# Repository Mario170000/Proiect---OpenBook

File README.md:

# Proiect---OpenBook
Proiectarea unui e-book reader open book

BOM:

| Qty | Value                   | Device                                                          | Parts                                                    | Description                                                                                                                                                                                                                           | WHERE_TO_BUY                                                                                                                                                                              | DATASHEET                                                                                                                            |
|-----|-------------------------|-----------------------------------------------------------------|----------------------------------------------------------|---------------------------------------------------------------------------------------------------------------------------------------------------------------------------------------------------------------------------------------|--------------------------------------------------------------------------------------------------------------------------------------------------------------------------------------------|-------------------------------------------------------------------------------------------------------------------------------------|
| 1   |                         | ADAFRUIT_LEDCHIP-LED0603                                        | CHG_LED                                                   | LED                                                                                                                                                                                                                                   | [link](https://ro.mouser.com/ProductDetail/BJB/35.116.1007-001-01?qs=iLKYxzqNS76jqQb6thkyzg%3D%3D)                                                                                          | [link](https://ro.mouser.com/datasheet/2/904/BJBDE_6680739_v3_Datasheet_35_116_1007_85_Optics4x-3193726.pdf)                                           |
| 3   |                         | EAGLE-LTSPICE_CC0402                                            | C4_USB, C5_USB, C17                                       | CAPACITOR, European symbol                                                                                                                                                                                                            | [link](https://ro.mouser.com/ProductDetail/YAGEO/CC0402KRX7R5BB474?qs=tS%2FAHvPQ%2F56tORtAcxAOhQ%3D%3D)                                                                                       | [link](https://ro.mouser.com/datasheet/2/447/UPY_GPHC_X7R_6_3V_to_250V_24-3441574.pdf)                                              |
| 1   |                         | SJ                                                              | SJ1                                                      | SMD solder JUMPER                                                                                                                                                                                                                     | [link](https://ro.mouser.com/ProductDetail/Amphenol-FCI/71363-302LF?qs=QPQicS5vByJvpVjU0oRgsQ%3D%3D)                                                                                        | [link](https://cdn.amphenol-cs.com/media/wysiwyg/files/documentation/datasheet/boardwiretoboard/bwb_dubox_shunts.pdf)                                 |
| 1   | 0.1uF/50V               | EAGLE-LTSPICE_CC0402                                            | EPD_C5                                                    | CAPACITOR, European symbol                                                                                                                                                                                                            | [link](https://ro.mouser.com/ProductDetail/YAGEO/CC0402JRX7R8BB104?qs=tS%2FAHvPQ%2F56C6Jcuby2Lxg%3D%3D)                                                                                        | [link](https://ro.mouser.com/datasheet/2/447/UPY_GPHC_X7R_6_3V_to_250V_24-3441574.pdf)                                              |
| 1   | 0.47                    | ESP32_WROVER_EAGLE-LTSPICE_RR0402                               | R4                                                        | RESISTOR, European symbol                                                                                                                                                                                                             | [link](https://ro.mouser.com/ProductDetail/Vishay/PFRR0402Y2101WBT?qs=iLKYxzqNS75ICTUqzuuuLQ%3D%3D)                                                                                           | [link](https://www.vishay.com/doc?53046)                                                                                                             |
| 1   | 100K                    | ESP32_WROVER_EAGLE-LTSPICE_RR0402                               | R1_PWRUSB                                                 | RESISTOR, European symbol                                                                                                                                                                                                             | [link](https://ro.mouser.com/ProductDetail/Vishay/PFRR0402Y1003WBT?qs=iLKYxzqNS76UwFIGpGXUcw%3D%3D)                                                                                           | [link](https://www.vishay.com/doc?53046)                                                                                                             |
| 7   | 100nF                   | EAGLE-LTSPICE_CC0402                                            | C1, C2, C6, C8, C9, C10, C_DELAY                          | CAPACITOR, European symbol                                                                                                                                                                                                            | [link](https://ro.mouser.com/ProductDetail/YAGEO/CC0402KRX7R5BB474?qs=tS%2FAHvPQ%2F56tORtAcxAOhQ%3D%3D)                                                                                       | [link](https://ro.mouser.com/datasheet/2/447/UPY_GPHC_X7R_6_3V_to_250V_24-3441574.pdf)                                              |
| 1   | 100uF                   | RCL_CPOL-EUCT3528                                               | C3                                                        | POLARIZED CAPACITOR, European symbol                                                                                                                                                                                                  | [link](https://ro.mouser.com/ProductDetail/Panasonic/EEU-FS1K101L?qs=sGAEpiMZZMvwFf0viD3Y3fHxNcSaiftwbgqrEa58hlq7Mz20qWHEdw%3D%3D)                                                              | [link](https://www.mouser.com/catalog/specsheets/Panasonic_08082018_Capacitor%20Radial%20Leaded%20Lytic%20(EEU-FS)%20020118.pdf)                      |
| 12  | 10K                     | ESP32_WROVER_EAGLE-LTSPICE_RR0402                               | R1_PINH, R1_PINH1, R2-PINH1, R2_PINH, R3, R5, R6, R7, R8, R9, R10, R_CL1 | RESISTOR, European symbol                                                                                                                                                                                                             | [link](https://ro.mouser.com/ProductDetail/Vishay/PFRR0402Y1002WBT?qs=iLKYxzqNS75QPApzdnOraw%3D%3D)                                                                                           | [link](https://www.vishay.com/doc?53046)                                                                                                             |
| 3   | 10k                     | ESP32_WROVER_EAGLE-LTSPICE_RR0402                               | R_BOOT, R_CHANGE, R_RESET                                 | RESISTOR, European symbol                                                                                                                                                                                                             | [link](https://ro.mouser.com/ProductDetail/Vishay/PFRR0402Y1002WBT?qs=iLKYxzqNS75QPApzdnOraw%3D%3D)                                                                                           | [link](https://www.vishay.com/doc?53046)                                                                                                             |
| 1   | 10uF                    | EAGLE-LTSPICE_CC0402                                            | C7                                                        | CAPACITOR, European symbol                                                                                                                                                                                                            | [link](https://ro.mouser.com/ProductDetail/YAGEO/CC0402MRX5R4BB106?qs=tS%2FAHvPQ%2F561gTjBOiVihQ%3D%3D)                                                                                        | [link](https://ro.mouser.com/datasheet/2/447/upy_gphc_x5r_4v_to_50v-3461255.pdf)                                                  |
| 1   | 112A-TAAR-R03_ATTEND                                        | 112A-TAAR-R03_ATTEND                                        | J4                                                        | Micro SD Card Socket, Push-Push Type, Top Mount, SMT, H=1.83mm, 10u                                                                                                                                                                    | [link](https://ro.mouser.com/ProductDetail/Swissbit/SFSD256GL2AM1TO-E-8H-231-STD?qs=%252BXxaIXUDbq3EiR9fdqsT0g%3D%3D)                                                                           | [link](https://ro.mouser.com/datasheet/2/615/Swissbit_02_03_2025_S_50_data_sheet-3561244.pdf)                                                         |
| 1   | 15                      | ESP32_WROVER_EAGLE-LTSPICE_RR0402                               | R_CAPACITOR                                               | RESISTOR, European symbol                                                                                                                                                                                                             | [link](https://ro.mouser.com/ProductDetail/Vishay/PFRR0402Y1002WBT?qs=iLKYxzqNS75QPApzdnOraw%3D%3D)                                                                                           | [link](https://www.vishay.com/doc?53046)                                                                                                             |
| 1   | 1uF                     | EAGLE-LTSPICE_CC0402                                            | C5                                                        | CAPACITOR, European symbol                                                                                                                                                                                                            | [link](https://ro.mouser.com/ProductDetail/YAGEO/CC0402KPX7R9BB332?qs=tS%2FAHvPQ%2F56Ev%2FR70%252BDkow%3D%3D)                                                                                   | [link](https://ro.mouser.com/datasheet/2/447/UPY_GPHC_X7R_6_3V_to_250V_24-3441574.pdf)                                              |
| 9   | 1uF/50V                 | EAGLE-LTSPICE_CC0402                                            | EPD_C1, EPD_C2, EPD_C6, EPD_C7, EPD_C8, EPD_C9, EPD_C10, EPD_C11, EPD_C12 | CAPACITOR, European symbol                                                                                                                                                                                                            | [link](https://ro.mouser.com/ProductDetail/YAGEO/CC0402KPX7R9BB332?qs=tS%2FAHvPQ%2F56Ev%2FR70%252BDkow%3D%3D)                                                                                   | [link](https://ro.mouser.com/datasheet/2/447/UPY_GPHC_X7R_6_3V_to_250V_24-3441574.pdf)                                              |
| 1   | 2.2                     | ESP32_WROVER_EAGLE-LTSPICE_RR0402                               | R2                                                        | RESISTOR, European symbol                                                                                                                                                                                                             | [link](https://ro.mouser.com/ProductDetail/Vishay/PFRR0402Y2201WBT?qs=iLKYxzqNS76BFrJRYiyDBw%3D%3D)                                                                                           | [link](https://www.vishay.com/doc?53046)                                                                                                             |
| 1   | 200                     | ESP32_WROVER_EAGLE-LTSPICE_RR0402                               | R1_BAT                                                    | RESISTOR, European symbol                                                                                                                                                                                                             | [link](https://ro.mouser.com/ProductDetail/Vishay/PFRR0402Y2101WBT?qs=iLKYxzqNS75ICTUqzuuuLQ%3D%3D)                                                                                           | [link](https://www.vishay.com/doc?53046)                                                                                                             |
| 2   | 20V/4.2A/52mO/1.4W      | ESP32_WROVER_SPARKFUN-DISCRETESEMI_MOSFET_PCH-DMG2305UX-7       | Q1, Q2                                                    | P-channel MOSFETs                                                                                                                                                                                                                     | [link](https://ro.mouser.com/ProductDetail/Diodes-Incorporated/DMG2305UX-7?qs=L1DZKBg7t5F%2FNBHrjfxC%252Bg%3D%3D)                                                                                | [link](https://www.diodes.com/assets/Datasheets/DMG2305UX.pdf)                                                                                         |
| 2   | 2K                      | ESP32_WROVER_EAGLE-LTSPICE_RR0402                               | R1, R2_BAT                                                | RESISTOR, European symbol                                                                                                                                                                                                             | [link](https://ro.mouser.com/ProductDetail/Vishay/PFRR0402Y2001WBT?qs=iLKYxzqNS75yWwLpEkqbdw%3D%3D)                                                                                           | [link](https://www.vishay.com/doc?53046)                                                                                                             |
| 4   | 4.7uF                   | EAGLE-LTSPICE_CC0402                                            | C1_BAT, C1_BAT2, C2_BAT, C4                               | CAPACITOR, European symbol                                                                                                                                                                                                            | [link](https://ro.mouser.com/ProductDetail/YAGEO/CC0402KRX5R6BB105?qs=BKNoF%2F0xMNu0TvpE6ze2Iw%3D%3D)                                                                                         | [link](https://ro.mouser.com/datasheet/2/447/upy_gphc_x5r_4v_to_50v-3461255.pdf)                                                  |
| 1   | 5K1                     | ESP32_WROVER_EAGLE-LTSPICE_RR0402                               | R2-USB1                                                   | RESISTOR, European symbol                                                                                                                                                                                                             | [link](https://ro.mouser.com/ProductDetail/Vishay/PFRR0402E4752BBT?qs=%252BXxaIXUDbq1vDshWgSXpwA%3D%3D)                                                                                         | [link](https://www.vishay.com/doc?53046)                                                                                                             |
| 1   | 5k1                     | ESP32_WROVER_EAGLE-LTSPICE_RR0402                               | R2-USB                                                    | RESISTOR, European symbol                                                                                                                                                                                                             | [link](https://ro.mouser.com/ProductDetail/Vishay/PFRR0402E4752BBT?qs=%252BXxaIXUDbq1vDshWgSXpwA%3D%3D)                                                                                         | [link](https://www.vishay.com/doc?53046)                                                                                                             |
| 1   | 68uH                    | 744043680IND_4828-WE-TPC_WRE                                    | L1                                                        |                                                                                                                                                                                                                                       | [link](https://ro.mouser.com/ProductDetail/Wurth-Elektronik/744043680?qs=PGXP4M47uW6VkZq%252BkzjrHA%3D%3D)                                                                                       | [link](https://www.we-online.com/components/products/datasheet/744043680.pdf)                                                                          |
| 1   | BD5229G-TR              | BD5229G-TR                                                     | IC1                                                       | Voltage Detector with Adjustable Delay Time: CMOS processes are utilized to develop high precision, low current consumption CMOS reset ICs that allow arbitrary setting of the delay time. | [link](https://ro.mouser.com/ProductDetail/ROHM-Semiconductor/BD5229G-TR?qs=4kLU8WoGk0vvnhrrYwdszw%3D%3D)                                                                                        | [link](https://fscdn.rohm.com/en/products/databook/datasheet/ic/power/voltage_detector/bd52xxg-e.pdf)                                                 |
| 3   | BUTTON_CUSYOMV1                                            | BUTTON_CUSYOMV1                                            | BOOT_BUTTON, CHANGE_BUTTON, RESET_BUTTON                 |                                                                                                                                                                                                                                       | [link](https://ro.mouser.com/ProductDetail/Bulgin/C7003SABR7?qs=5aG0NVq1C4zkqomKc3HwTQ%3D%3D)                                                                                                  | [link](https://www.bulgin.com/products/pub/media/bulgin/data/A_Push%20button.pdf)                                                                      |
| 1   | CPH3225A                                                    | CPH3225A                                                    | C10_SUPERCAP                                              | Cap 0.011F 3.3V 1210 Flat Check availability                                                                                                                                                                                          | [link](https://ro.mouser.com/ProductDetail/Seiko-Semiconductors/CPH3225A?qs=3etwrb1wR%252BhUOph6lAO7eg%3D%3D)                                                                                    | [link](https://ro.mouser.com/datasheet/2/360/Seiko_Instruments_MicroBattery_E_20230330_2024Jan_-3561061.pdf)                                           |
| 1   | DS3231SN#                                                  | DS3231SN#                                                  | U3                                                        | Real Time Clock Serial 16-Pin SOIC W T/R     Check availability                                                                                                                                                                       | [link](https://ro.mouser.com/ProductDetail/Analog-Devices-Maxim-Integrated/DS3231SN?qs=1eQvB6Dk1vhUlr8%2FOrV0Fw%3D%3D)                                                                            | [link](https://ro.mouser.com/datasheet/2/609/DS3231-3421123.pdf)                                                                                       |
| 1   | ESP32-C6-WROOM-1-N8                                        | ESP32-C6-WROOM-1-N8                                        | U2                                                        | Check availability                                                                                                                                                                                                                    | [link](https://ro.mouser.com/ProductDetail/Espressif-Systems/ESP32-C6-WROOM-1-N8?qs=8Wlm6%252BaMh8ST02Gmwp74cw%3D%3D)                                                                               | [link](https://ro.mouser.com/datasheet/2/891/Espressif_ESP32_C6_WROOM_1__Datasheet_V0_1_PRELIMI-3239987.pdf)                                           |
| 1   | ESP32C6_VARISTORCN1812                                      | ESP32C6_VARISTORCN1812                                      | PFMP.050.1                                                | VARISTOR                                                                                                                                                                                                                              | [link](https://ro.mouser.com/ProductDetail/EPCOS-TDK/B72580V3140S272?qs=v4Mlc8l4PHkyDvCWZ8i%252Bvg%3D%3D)                                                                                         | [link](https://en.tdk.eu/inf/75/db/CTVS_14/Surge_protection_series.pdf)                                                                                |
| 2   | ESP32_WROVER_AVX---SD0805S020S1R0_AVX_SD0805S020S1R0_0_0AVX_SD0805S020S1R0_0_0 | ESP32_WROVER_AVX---SD0805S020S1R0_AVX_SD0805S020S

## ESP32-C6 Pinout

| Pin | Name        | Function                             |
|-----|-------------|--------------------------------------|
| 1   | GND         | Common ground                        |
| 2   | 3V3         | Power line                           |
| 3   | RESET       | Reset button                         |
| 4   | SS_SD       | SD card chip select                  |
| 5   | EPD_DC      | E-Paper Display Data/Command         |
| 6   | SCK         | SPI Clock for BME688                 |
| 7   | MOSI        | SPI Master Out Slave In              |
| 8   | INT_RTC     | RTC Interrupt (DS3231SN)             |
| 9   | 32KHZ       | RTC 32kHz output                     |
| 10  | 3V3/GPIO8   | Power line                           |
| 11  | EPD_CS      | E-Paper Display Chip Select          |
| 12  | FLASH_CS    | External NOR Flash (64MB)            |
| 13  | USB_D-      | USB D- line                          |
| 14  | USB_D+      | USB D+ line                          |
| 15  | IO/BOOT     | BOOT button                          |
| 16  | RTC_RST     | RTC Module Reset (DS3231SN)          |
| 17  | I2C_PW      | BME688 power line                    |
| 18  | EPD_3V3_C   | EPD Power                            |
| 19  | SDA         | Battery charge level (I²C)           |
| 20  | SCL         | Battery SCL (I²C)                    |
| 21  | EPD_RST     | E-Paper Display Reset                |
| 22  | X           | Not in use                           |
| 23  | IO/CHANGE   | User button                          |
| 24  | RX          | UART RX for debugging                |
| 25  | TX          | UART TX for debugging                |
| 26  | EPD_BUSY    | E-Paper Display Busy signal          |
| 27  | MISO        | SPI Master In Slave Out              |

# Hardware Components Overview

This section provides a detailed description of the key hardware components used in the OpenBook project.

## ESP32-C6-WROOM-1-N8
The **ESP32-C6-WROOM-1-N8** is a powerful Wi-Fi 6 and Bluetooth 5 LE module based on the ESP32-C6 SoC, with 8MB of integrated flash. It features a RISC-V processor and provides low-power connectivity for IoT applications. In this project, it acts as the **main microcontroller**, handling data acquisition, processing, and wireless communication.

## BME680
The **BME680** is a 4-in-1 environmental sensor that measures **temperature, humidity, barometric pressure, and air quality (VOC)**. It communicates via I²C or SPI. In this device, it provides ambient condition monitoring, enabling features like smart display behavior or indoor air quality feedback.

## MCP73831T-2ACI/OT
The **MCP73831** is a **Li-Ion/Li-Po linear battery charger** IC, supporting single-cell charging through a constant-current/constant-voltage algorithm. It is used to safely charge the onboard Li-Po battery when the device is connected to USB power.

## W25Q512JVEIQ
The **W25Q512JVEIQ** is a **512M-bit (64MB) SPI NOR Flash memory** from Winbond. It provides additional non-volatile storage space, useful for storing large assets such as e-books, sensor logs, or firmware updates. It is connected via SPI to the ESP32.

## USBLC6-2SC6Y
The **USBLC6-2SC6Y** is a **dual-line ESD protection device** designed to protect USB data lines from electrostatic discharge. It ensures signal integrity and protects the USB interface (D+ and D−) from damage, especially during hot-plug events or electrostatic contact.

## 112A-TAAR-R03
The **112A-TAAR-R03** is a **mechanical tactile push button switch**, typically used for user input. In this project, it serves as a **physical interface**, such as page turning, menu selection, or device wake-up. It is connected to GPIOs on the ESP32 and configured with internal pull-up resistors.

## USB4110-GF-A
The **USB4110-GF-A** is a **USB Type-C receptacle connector**. It provides the physical interface for USB charging and communication. It connects to the USB-to-UART circuitry (or directly to ESP32 if used in native USB mode) and to the battery charging IC.

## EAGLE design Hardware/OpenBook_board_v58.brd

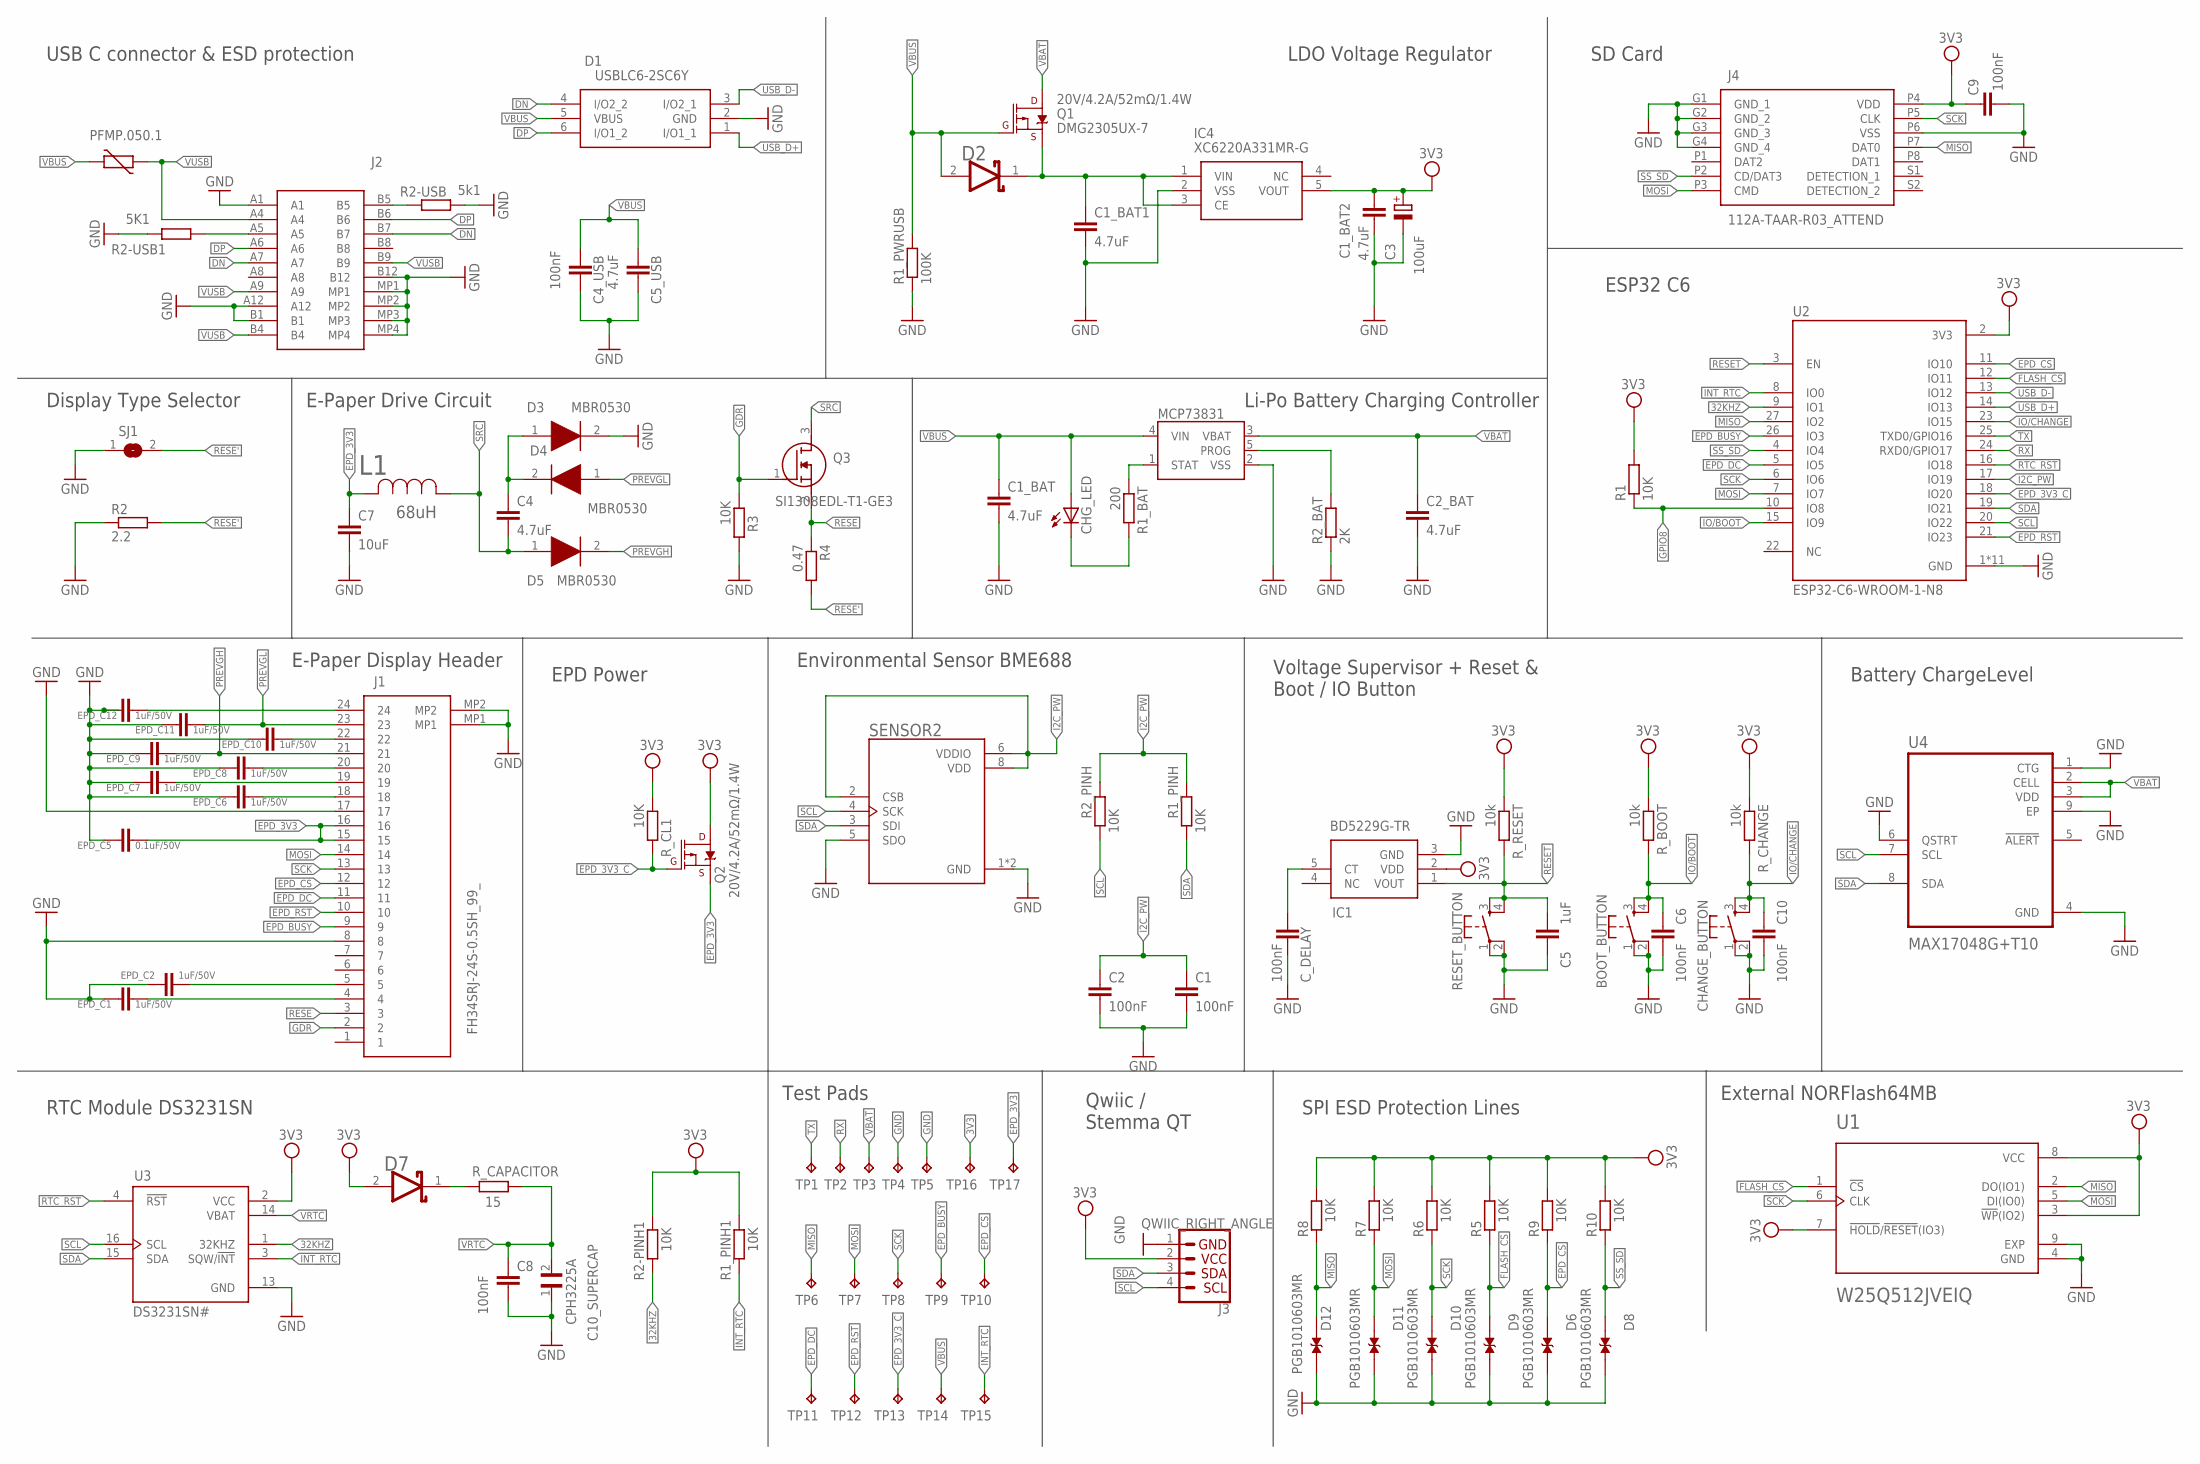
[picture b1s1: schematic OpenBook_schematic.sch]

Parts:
BOOT_BUTTON: BUTTON_CUSYOMV1; MYBUTTON
C1, C2, C4_USB, C6, C8, C9, C10: 100nF; EAGLE-LTSPICE_C0402
C1_BAT, C1_BAT1, C1_BAT2, C2_BAT, C4, C5_USB: 4.7uF; EAGLE-LTSPICE_C0402
C3: 100uF; RCL_CT3528
C5: 1uF; EAGLE-LTSPICE_C0402
C7: 10uF; EAGLE-LTSPICE_C0402
C10_SUPERCAP: CPH3225A; CAPCP3225X100N
CHANGE_BUTTON: BUTTON_CUSYOMV1; MYBUTTON
CHG_LED: ADAFRUIT_LEDCHIP-LED0603; ADAFRUIT_CHIP-LED0603
C_DELAY: 100nF; EAGLE-LTSPICE_C0402
D1: USBLC6-2SC6Y; SOT95P280X145-6N
D2, D7: ESP32_WROVER_AVX---SD0805S020S1R0_AVX_SD0805S020S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; ESP32_WROVER_AVX---SD0805S020S1R0_AVX_SD0805S020S1R0_0
D3, D4, D5: MBR0530; SOD3716X135N
D6, D8, D9, D10, D11, D12: PGB1010603MR; DIOC1608X36N
EPD_C1, EPD_C2, EPD_C6, EPD_C7, EPD_C8, EPD_C9, EPD_C10, EPD_C11, EPD_C12: 1uF/50V; EAGLE-LTSPICE_C0402
EPD_C5: 0.1uF/50V; EAGLE-LTSPICE_C0402
IC1: BD5229G-TR; SOT95P280X125-5N
IC4: XC6220A331MR-G; SOT95P280X120-5N
J1: FH34SRJ-24S-0.5SH_99_; FH34SRJ24S05SH99
J2: SAMACSYS_PARTS_USB4110-GF-A; SAMACSYS_PARTS_USB4110GFA
J3: QWIIC_RIGHT_ANGLE; JST04_1MM_RA
J4: 112A-TAAR-R03_ATTEND; 112ATAARR03ATTEND
L1: 68uH; IND_4828-WE-TPC_WRE
MCP73831: ESP32_WROVER_SPARKFUN-IC-POWER_MCP73831; ESP32_WROVER_SPARKFUN-IC-POWER_SOT23-5
PFMP.050.1: ESP32C6_VARISTORCN1812; ESP32C6_VARISTOR_CT/CN1812
Q1, Q2: 20V/4.2A/52mΩ/1.4W; ESP32_WROVER_SPARKFUN-DISCRETESEMI_SOT23-3
Q3: SI1308EDL-T1-GE3; SOT65P210X110-3N
R1, R1_PINH, R1_PINH1, R2-PINH1, R2_PINH, R3, R5, R6, R7, R8, R9, R10: 10K; ESP32_WROVER_EAGLE-LTSPICE_R0402
R1_BAT: 200; ESP32_WROVER_EAGLE-LTSPICE_R0402
R1_PWRUSB: 100K; ESP32_WROVER_EAGLE-LTSPICE_R0402
R2: 2.2; ESP32_WROVER_EAGLE-LTSPICE_R0402
R2-USB: 5k1; ESP32_WROVER_EAGLE-LTSPICE_R0402
R2-USB1: 5K1; ESP32_WROVER_EAGLE-LTSPICE_R0402
R2_BAT: 2K; ESP32_WROVER_EAGLE-LTSPICE_R0402
R4: 0.47; ESP32_WROVER_EAGLE-LTSPICE_R0402
RESET_BUTTON: BUTTON_CUSYOMV1; MYBUTTON
R_BOOT: 10k; ESP32_WROVER_EAGLE-LTSPICE_R0402
R_CAPACITOR: 15; ESP32_WROVER_EAGLE-LTSPICE_R0402
R_CHANGE: 10k; ESP32_WROVER_EAGLE-LTSPICE_R0402
R_CL1: 10K; ESP32_WROVER_EAGLE-LTSPICE_R0402
R_RESET: 10k; ESP32_WROVER_EAGLE-LTSPICE_R0402
SENSOR2: ESP32_WROVER_BME680_BME680; ESP32_WROVER_BME680_PSON80P300X300X100-8N
SJ1: SJ
TP1, TP2, TP3, TP4, TP5, TP6, TP7, TP8, TP9, TP10, TP11, TP12, TP13, TP14, TP15, TP16, TP17: TPTP20R; TP20R
U1: W25Q512JVEIQ; SON127P600X800X80-9N
U2: ESP32-C6-WROOM-1-N8; XCVR_ESP32-C6-WROOM-1-N8
U3: DS3231SN#; SOIC127P1032X265-16N
U4: MAX17048G+T10; SON50P200X200X80-9N

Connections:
3V3: C1_BAT2.1, C3.+, C9.1, D7.2 (ANODE), IC1.2 (VDD), IC4.5 (VOUT), J3.2, J4.P4 (VDD), Q2.3 (D), R1.2, R1_PINH1.2, R2-PINH1.2, R5.2, R6.2, R7.2, R8.2, R9.2, R10.2, R_BOOT.1, R_CHANGE.1, R_CL1.1, R_RESET.1, TP16.TP, U1.3 (!WP!(IO2)), U1.7 (!HOLD!/!RESET!(IO3)), U1.8 (VCC), U2.2 (3V3), U3.2 (VCC)
32KHZ: R2-PINH1.1, U2.9 (IO1), U3.1 (32KHZ)
DN: D1.4 (I/O2_2), J2.A7, J2.B7
DP: D1.6 (I/O1_2), J2.A6, J2.B6
EPD_3V3: C7.1, EPD_C5.1, J1.15, J1.16, L1.2, Q2.2 (S), TP17.TP
EPD_3V3_C: Q2.1 (G), R_CL1.2, TP13.TP, U2.18 (IO20)
EPD_BUSY: J1.9, TP9.TP, U2.26 (IO3)
EPD_CS: D6.2, J1.12, R9.1, TP10.TP, U2.11 (IO10)
EPD_DC: J1.11, TP11.TP, U2.5 (IO5)
EPD_RST: J1.10, TP12.TP, U2.21 (IO23)
FLASH_CS: D9.2, R5.1, U1.1 (!CS), U2.12 (IO11)
GDR: J1.2, Q3.1 (G), R3.1
GND: BOOT_BUTTON.1, BOOT_BUTTON.2, C1.2, C1_BAT.2, C1_BAT1.2, C1_BAT2.2, C2.2, C2_BAT.2, C3.-, C4_USB.2, C5.2, C5_USB.2, C6.2, C7.2, C8.2, C9.2, C10.2, C10_SUPERCAP.1, CHANGE_BUTTON.1, CHANGE_BUTTON.2, C_DELAY.2, D1.2 (GND), D3.2 (K), D6.1, D8.1, D9.1, D10.1, D11.1, D12.1, EPD_C1.2, EPD_C2.2, EPD_C5.2, EPD_C6.2, EPD_C7.2, EPD_C8.2, EPD_C9.2, EPD_C10.2, EPD_C11.2, EPD_C12.2, IC1.3 (GND), IC4.2 (VSS), J1.8, J1.17, J1.MP1, J1.MP2, J2.A1, J2.A12, J2.B1, J2.B12, J2.MP1, J2.MP2, J2.MP3, J2.MP4, J3.1, J4.G1 (GND_1), J4.G2 (GND_2), J4.G3 (GND_3), J4.G4 (GND_4), J4.P6 (VSS), MCP73831.2 (VSS), R1_PWRUSB.1, R2.1, R2-USB.2, R2-USB1.1, R2_BAT.1, R3.2, RESET_BUTTON.1, RESET_BUTTON.2, SENSOR2.1 (GND), SENSOR2.5 (SDO), SENSOR2.7 (GND), SJ1.1, TP4.TP, TP5.TP, U1.4 (GND), U1.9 (EXP), U2.1 (GND), U2.28 (GND), U2.29_1 (GND), U2.29_2 (GND), U2.29_3 (GND), U2.29_4 (GND), U2.29_5 (GND), U2.29_6 (GND), U2.29_7 (GND), U2.29_8 (GND), U2.29_9 (GND), U3.13 (GND), U4.1 (CTG), U4.4 (GND), U4.6 (QSTRT), U4.9 (EP)
GPIO8: R1.1, U2.10 (IO8)
I2C_PW: C1.1, C2.1, R1_PINH.2, R2_PINH.2, SENSOR2.2 (CSB), SENSOR2.6 (VDDIO), SENSOR2.8 (VDD), U2.17 (IO19)
INT_RTC: R1_PINH1.1, TP15.TP, U2.8 (IO0), U3.3 (SQW/!INT)
IO/BOOT: BOOT_BUTTON.3, BOOT_BUTTON.4, C6.1, R_BOOT.2, U2.15 (IO9)
IO/CHANGE: C10.1, CHANGE_BUTTON.3, CHANGE_BUTTON.4, R_CHANGE.2, U2.23 (IO15)
MISO: D12.2, J4.P7 (DAT0), R8.1, TP6.TP, U1.2 (DO(IO1)), U2.27 (IO2)
MOSI: D11.2, J1.14, J4.P3 (CMD), R7.1, TP7.TP, U1.5 (DI(IO0)), U2.7 (IO7)
unnamed: J2.B5, R2-USB.1
unnamed: EPD_C12.1, J1.24
unnamed: J2.A5, R2-USB1.2
unnamed: C1_BAT1.1, D2.1 (CATHODE), IC4.1 (VIN), IC4.3 (CE), Q1.2 (S)
unnamed: MCP73831.1 (STAT), R1_BAT.1
unnamed: CHG_LED.C, R1_BAT.2
unnamed: C4.1, D3.1 (A), D4.2 (K)
unnamed: EPD_C6.1, J1.18
unnamed: MCP73831.5 (PROG), R2_BAT.2
unnamed: EPD_C1.1, J1.4
unnamed: EPD_C2.1, J1.5
unnamed: C_DELAY.1, IC1.5 (CT)
unnamed: EPD_C7.1, J1.19
unnamed: EPD_C8.1, J1.20
unnamed: EPD_C10.1, J1.22
unnamed: D7.1 (CATHODE), R_CAPACITOR.2
PREVGH: D5.2 (K), EPD_C9.1, J1.21
PREVGL: D4.1 (A), EPD_C11.1, J1.23
RESE: J1.3, Q3.2 (S), R4.1
RESE': R2.2, R4.2, SJ1.2
RESET: C5.1, IC1.1 (VOUT), RESET_BUTTON.3, RESET_BUTTON.4, R_RESET.2, U2.3 (EN)
RTC_RST: U2.16 (IO18), U3.4 (!RST)
RX: TP2.TP, U2.24 (RXD0/GPIO17)
SCK: D10.2, J1.13, J4.P5 (CLK), R6.1, TP8.TP, U1.6 (CLK), U2.6 (IO6)
SCL: J3.4, R2_PINH.1, SENSOR2.4 (SCK), U2.20 (IO22), U3.16 (SCL), U4.7 (SCL)
SDA: J3.3, R1_PINH.1, SENSOR2.3 (SDI), U2.19 (IO21), U3.15 (SDA), U4.8 (SDA)
SRC: C4.2, D5.1 (A), L1.1, Q3.3 (D)
SS_SD: D8.2, J4.P2 (CD/DAT3), R10.1, U2.4 (IO4)
TX: TP1.TP, U2.25 (TXD0/GPIO16)
USB_D+: D1.1 (I/O1_1), U2.14 (IO13)
USB_D-: D1.3 (I/O2_1), U2.13 (IO12)
VBAT: C2_BAT.1, MCP73831.3 (VBAT), Q1.3 (D), TP3.TP, U4.2 (CELL), U4.3 (VDD)
VBUS: C1_BAT.1, C4_USB.1, C5_USB.1, CHG_LED.A, D1.5 (VBUS), D2.2 (ANODE), MCP73831.4 (VIN), PFMP.050.1.2, Q1.1 (G), R1_PWRUSB.2, TP14.TP
VRTC: C8.1, C10_SUPERCAP.2, R_CAPACITOR.1, U3.14 (VBAT)
VUSB: J2.A4, J2.A9, J2.B4, J2.B9, PFMP.050.1.1

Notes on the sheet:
USB C connector & ESD protection
SD Card
LDO Voltage Regulator
Display Type Selector
E-Paper Drive Circuit
Li-Po Battery Charging Controller
ESP32 C6
E-Paper Display Header
EPD Power
Environmental Sensor BME688
Voltage Supervisor + Reset & Boot / IO Button
Battery ChargeLevel
RTC Module DS3231SN
Test Pads
Qwiic / Stemma QT
SPI ESD Protection Lines
External NORFlash64MB
DMG2305UX-7

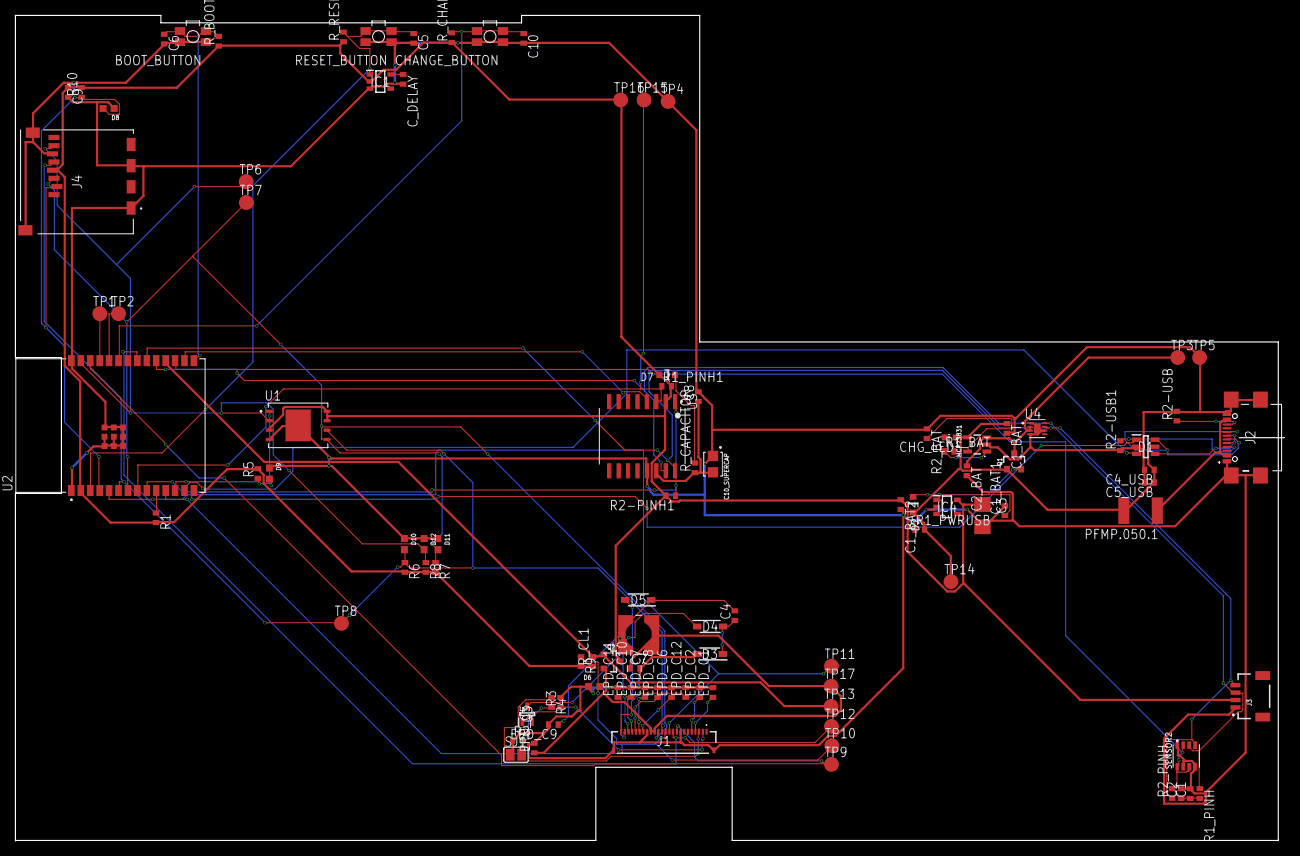
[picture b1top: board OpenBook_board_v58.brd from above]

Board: 2 copper layers, 171.0 x 111.2 mm, 103 parts (0 on the bottom side), 55 nets.

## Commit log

2025-03-19 Added the schematic file for the e-book reader
2025-04-06 Added a GNU license for the project
2025-04-06 Added images for the device
2025-04-06 Final README
2025-04-06 Added Schematic(.sch) as well as Board(.brd)
2025-04-06 Finised both 3D files
2025-04-06 Gerbers, BOM and Pick_and_Place done
2025-04-06 A final touch to README
2025-04-06 Deleted the file from the wrong location
2025-04-14 Replaced board and schematic with the correct ones.
2025-04-14 Updated mechanical
2025-04-14 Added rendered photos of battery and display
2025-04-14 Added rendered images for battery and display
2025-04-14 Updated images
2025-04-14 Updated exploded view photo
2025-04-15 Final brd
2025-04-15 Final step and 3d

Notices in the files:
parts and their libraries:
COPYRIGHT: Copyright (C) 2024 Ultra Librarian. All rights reserved.
